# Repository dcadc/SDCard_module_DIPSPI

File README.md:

# SDCard_module_DIPSPI
這是一個和 Taiwanduino 相容的 microSD 記憶卡擴充板  
他可以直接取代原本所使用的 25AA512 EEPROM 記憶體

**使用說明**
* TaiwanDuino :   
 [/software/Taiwanduino/example][sw] 資料夾內的程式碼使用 Arduino IDE 開啟  
 預設播放檔名為 0.wav ~ 7.wav 的 PCM 編碼音訊檔  
 [安裝相對應的程式庫][libs]之後即可編譯上傳  
  
*** 
  
*Read this in other languages: [English](README.en.md), [正體中文](README.md).*  

   [sw]: <https://github.com/dcadc/SDCard_module_DIPSPI/tree/master/software/Taiwanduino/example/>
   [libs]: <https://github.com/dcadc/SDCard_module_DIPSPI/blob/master/software/Taiwanduino/README.md>

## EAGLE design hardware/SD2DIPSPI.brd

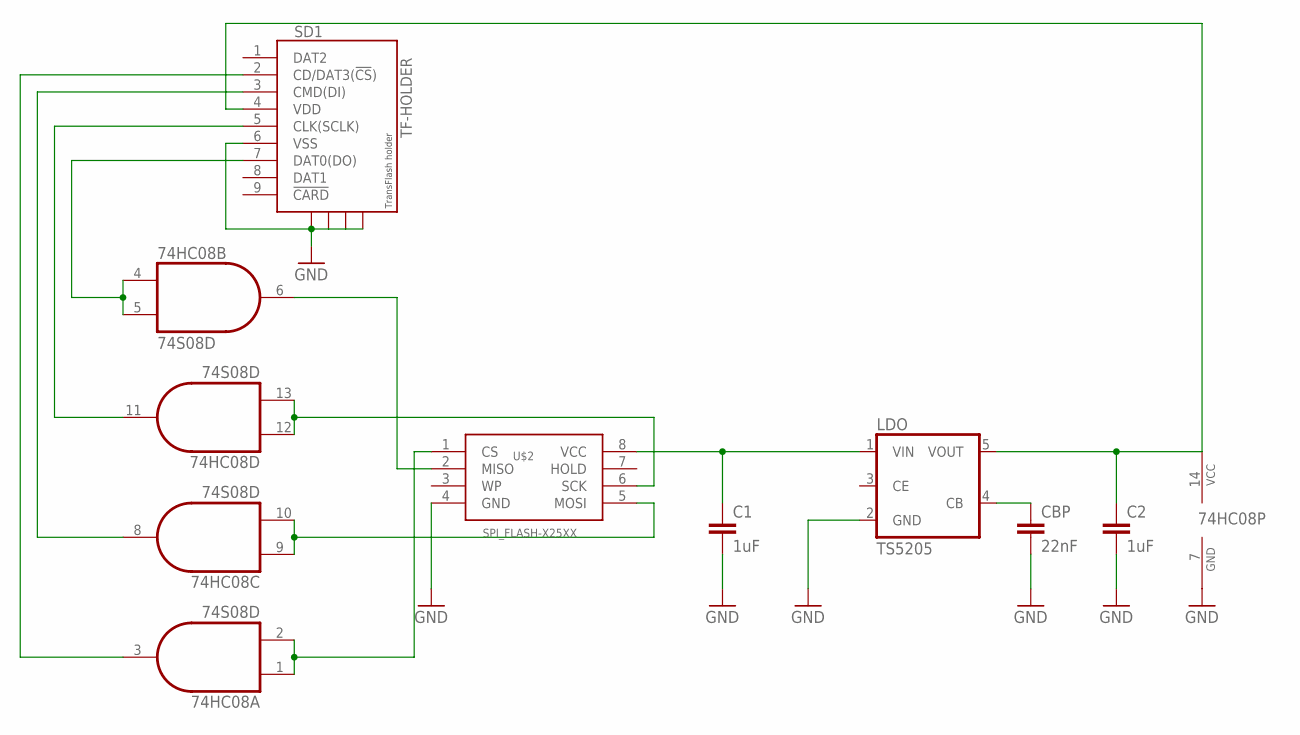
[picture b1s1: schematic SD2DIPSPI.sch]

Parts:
74HC08: 74S08D; SO14
C1, C2: 1uF; 0603-CAP
CBP: 22nF; 0402-CAP
LDO: TS5205; SOT25
SD1: TF-HOLDER; TF-PULL
U$2: SPI_FLASH-X25XX; DIL08

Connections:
3V3: 74HC08.14 (VCC), C2.1, LDO.5 (VOUT), SD1.4 (VDD)
+5V: C1.1, LDO.1 (VIN), U$2.8 (VCC)
GND: 74HC08.7 (GND), C1.2, C2.2, CBP.2, LDO.2 (GND), SD1.6 (VSS), SD1.S1, SD1.S2, SD1.S3, SD1.S4, U$2.4 (GND)
unnamed: CBP.1, LDO.4 (CB)
unnamed: 74HC08.9 (I0), 74HC08.10 (I1), U$2.5 (MOSI)
unnamed: 74HC08.12 (I0), 74HC08.13 (I1), U$2.6 (SCK)
unnamed: 74HC08.1 (I0), 74HC08.2 (I1), U$2.1 (CS)
unnamed: 74HC08.11 (O), SD1.5 (CLK(SCLK))
unnamed: 74HC08.8 (O), SD1.3 (CMD(DI))
unnamed: 74HC08.3 (O), SD1.2 (CD/DAT3(!CS!))
unnamed: 74HC08.6 (O), U$2.2 (MISO)
unnamed: 74HC08.4 (I0), 74HC08.5 (I1), SD1.7 (DAT0(DO))

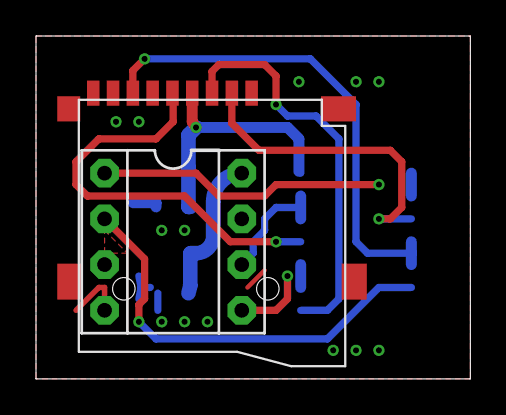
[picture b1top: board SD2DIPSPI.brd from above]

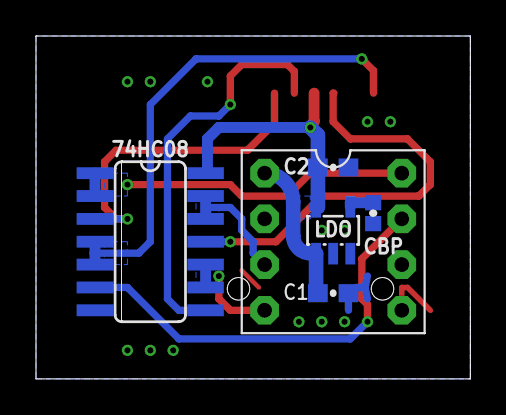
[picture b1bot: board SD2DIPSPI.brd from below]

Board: 2 copper layers, 24.1 x 19.1 mm, 7 parts (5 on the bottom side), 12 nets.

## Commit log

2016-10-27 :octocat: Added .gitattributes
2016-10-27 fix readme
2016-11-11 library issue fixed
    switched to original CapacitiveSensor library instead of the costomized
    one
2017-04-10 Seperate english version
2017-04-10 Seperated from README.md
2017-04-10 fix links
2017-04-10 fix procedures
2017-04-10 Create English version
2017-07-07 reorganize hardware resource

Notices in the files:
parts and their libraries:
SparkFun-Capacitors: Licensing: CC v3.0 Share-Alike You are welcome to use this library for commercial purposes.
SparkFun-DigitalIC: Licensing: Creative Commons ShareAlike 4.0 International - https://creativecommons.org/licenses/by-sa/4.0
